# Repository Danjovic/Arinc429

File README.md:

# Arinc429
Arinc 429 related projects

## Arinc 429 RX / MONITOR

Interrupt driven Arinc429 receiver code for use with  [HOLT IC](https://www.holtic.com/) line receiver [HI-8588](http://www.holtic.com/documents/76-hi-8588_v-rev-epdf.do).

### Features:
- ATMega88/328 based
- Text based User Interface
- Display labels of the messages
- Shows information of a message with an specific label or all messages
- Message interval meter (1m resolution)
- Data fields can be displayed in either binary or hexadecimal format
- Line load measurement
- Verbose level selection  
- Released under [GPL V3](https://www.gnu.org/licenses/gpl-3.0.html);

### Connections
|  AVR  |  HI-8588 pin  |
| ----------- | ----------- |
|  PD2/INT0  |  ROUTB (7)  |
|  PD3/INT1  |  ROUTA (6)  | 

## Arinc 429 TX

Interrupt driven Arinc429 transmit code for use with  [HOLT IC](https://www.holtic.com/)  drivers [HI-8585/HI-8586](http://www.holtic.com/documents/85-hi-8585_v-rev-ppdf.do).

### Features:
- ATMegaxx8 based
- Scheduler with 1ms resolution for 64 messages;
- Transmission queue with 64 entries;
- Scheduler and Transmission queue can be increased up to the extent of RAM available;
- Low CPU consumption, roughly 15% (~6us out of each 40us for ATmega running @16MHz);
- Bit fields to access Label, Data, SSM, SDI and parity;
- Programmable Intergap Message (down to zero);
- Messagens can be silenced;
- Macros to drive pins to debug like 32 bits SPI on logic analyzers; 
- Can be compiled within Arduino IDE, or externally (Makefile for AVR-GCC provided);
- Released under [GPL V3](https://www.gnu.org/licenses/gpl-3.0.html);

### Connections
|  AVR  |  HI-8585/8586 pin  |
| ----------- | ----------- |
|  PB1  |  TX1IN (3)  |
|  PB2  |  TX0IN (2)  | 

#### SPI Style debuging
|  AVR  |  SPI pin  |
| ----------- | ----------- |
|  PB1  |  MOSI (TX1IN)  |
|  PB2  |  MISO (TX0IN)  | 
|  PB3  |  CLOCK  |
|  PB4  |  /SELECT  | 

##### SPI style debug

##### single bit processing time

##### Scheduler in action

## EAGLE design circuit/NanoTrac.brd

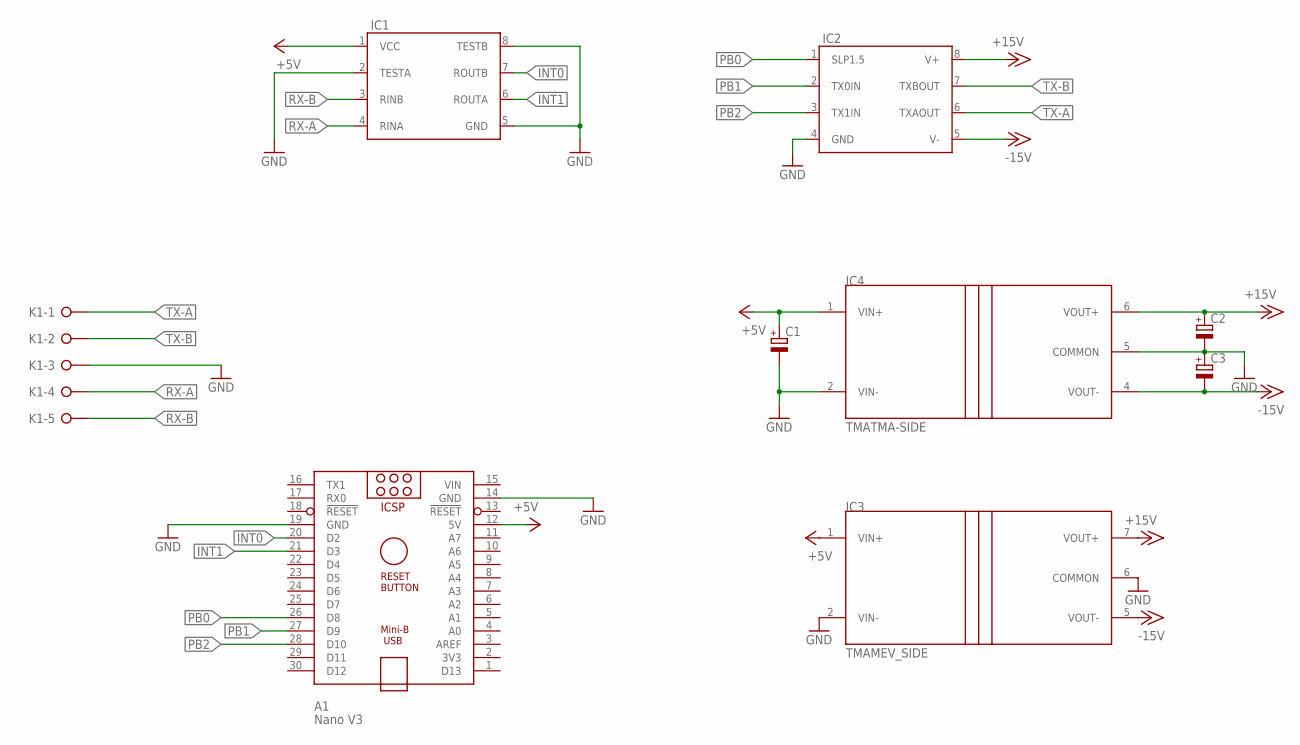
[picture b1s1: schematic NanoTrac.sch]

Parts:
A1: Nano V3; ARDUINO_NANO
C1, C2, C3: CPOL-EUE2-4; E2-4
IC1: HI-8588HN; SOIC8
IC2: HI-8586HN; SOIC8
IC3: TMAMEV_SIDE; MEV_SIP7_SIDE
IC4: TMATMA-SIDE; SIP7_SIDE
K1: W237-05P; W237-5P

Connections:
+5V: A1.12 (5V), C1.+, IC1.1 (VCC), IC3.1 (VIN+), IC4.1 (VIN+)
+15V: C2.+, IC2.8 (V+), IC3.7 (VOUT+), IC4.6 (VOUT+)
-15V: C3.-, IC2.5 (V-), IC3.5 (VOUT-), IC4.4 (VOUT-)
GND: A1.14 (GND), A1.19 (GND), C1.-, C2.-, C3.+, IC1.2 (TESTA), IC1.5 (GND), IC1.8 (TESTB), IC2.4 (GND), IC3.2 (VIN-), IC3.6 (COMMON), IC4.2 (VIN-), IC4.5 (COMMON), K1.3
INT0: A1.20 (D2), IC1.7 (ROUTB)
INT1: A1.21 (D3), IC1.6 (ROUTA)
PB0: A1.26 (D8), IC2.1 (SLP1.5)
PB1: A1.27 (D9), IC2.2 (TX0IN)
PB2: A1.28 (D10), IC2.3 (TX1IN)
RX-A: IC1.4 (RINA), K1.4
RX-B: IC1.3 (RINB), K1.5
TX-A: IC2.6 (TXAOUT), K1.1
TX-B: IC2.7 (TXBOUT), K1.2
VIN: A1.15 (VIN)

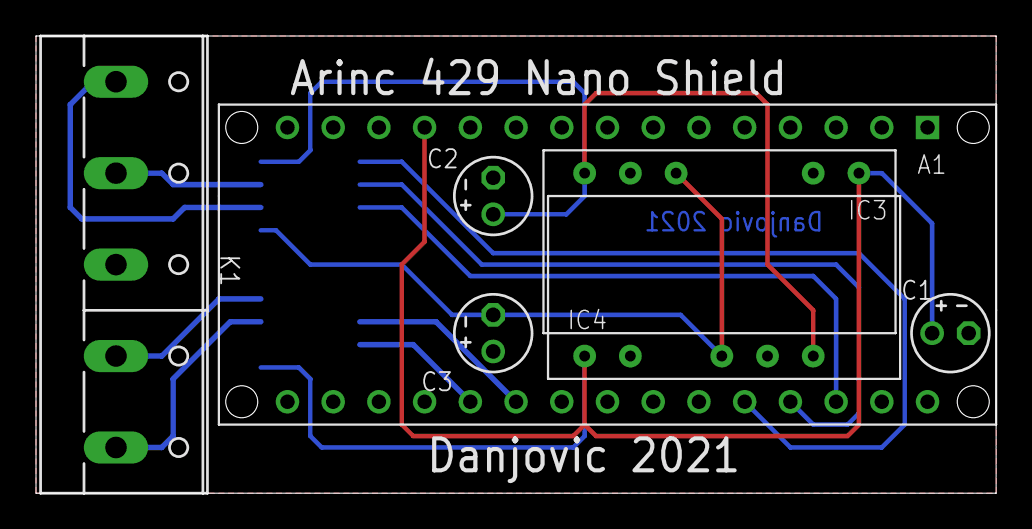
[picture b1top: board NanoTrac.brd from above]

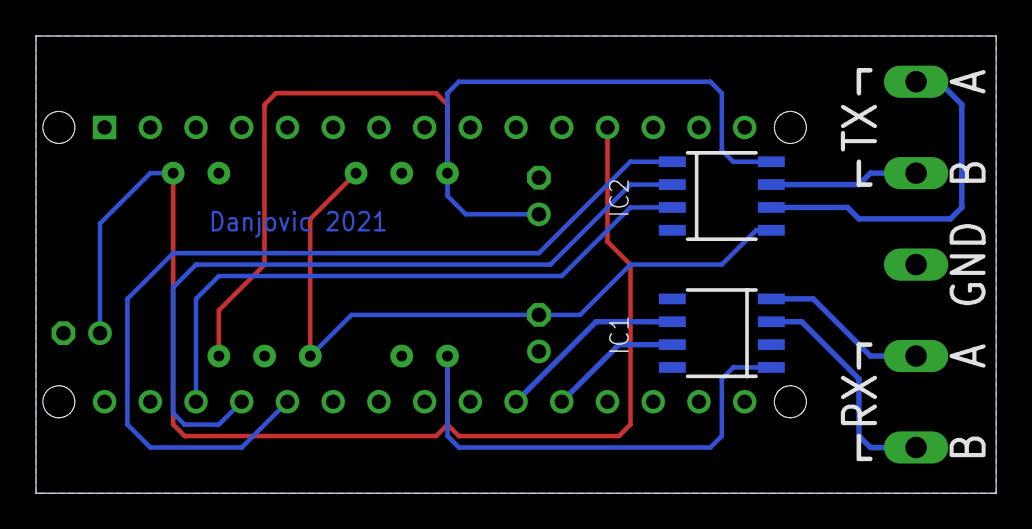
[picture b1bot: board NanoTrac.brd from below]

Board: 2 copper layers, 53.3 x 25.4 mm, 9 parts (2 on the bottom side), 13 nets.

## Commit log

2021-05-01 Added Transmit Code
2021-05-01 updated images
2021-05-01 updated files
2023-05-06 Added Arinc 429 RX / Line Monitor
2023-05-06 Cleanup
2026-06-21 fix bus load measurement
2026-06-23 small fixes
2026-06-23 fixed bit field order
2026-06-25 small improvement on "A" mode
